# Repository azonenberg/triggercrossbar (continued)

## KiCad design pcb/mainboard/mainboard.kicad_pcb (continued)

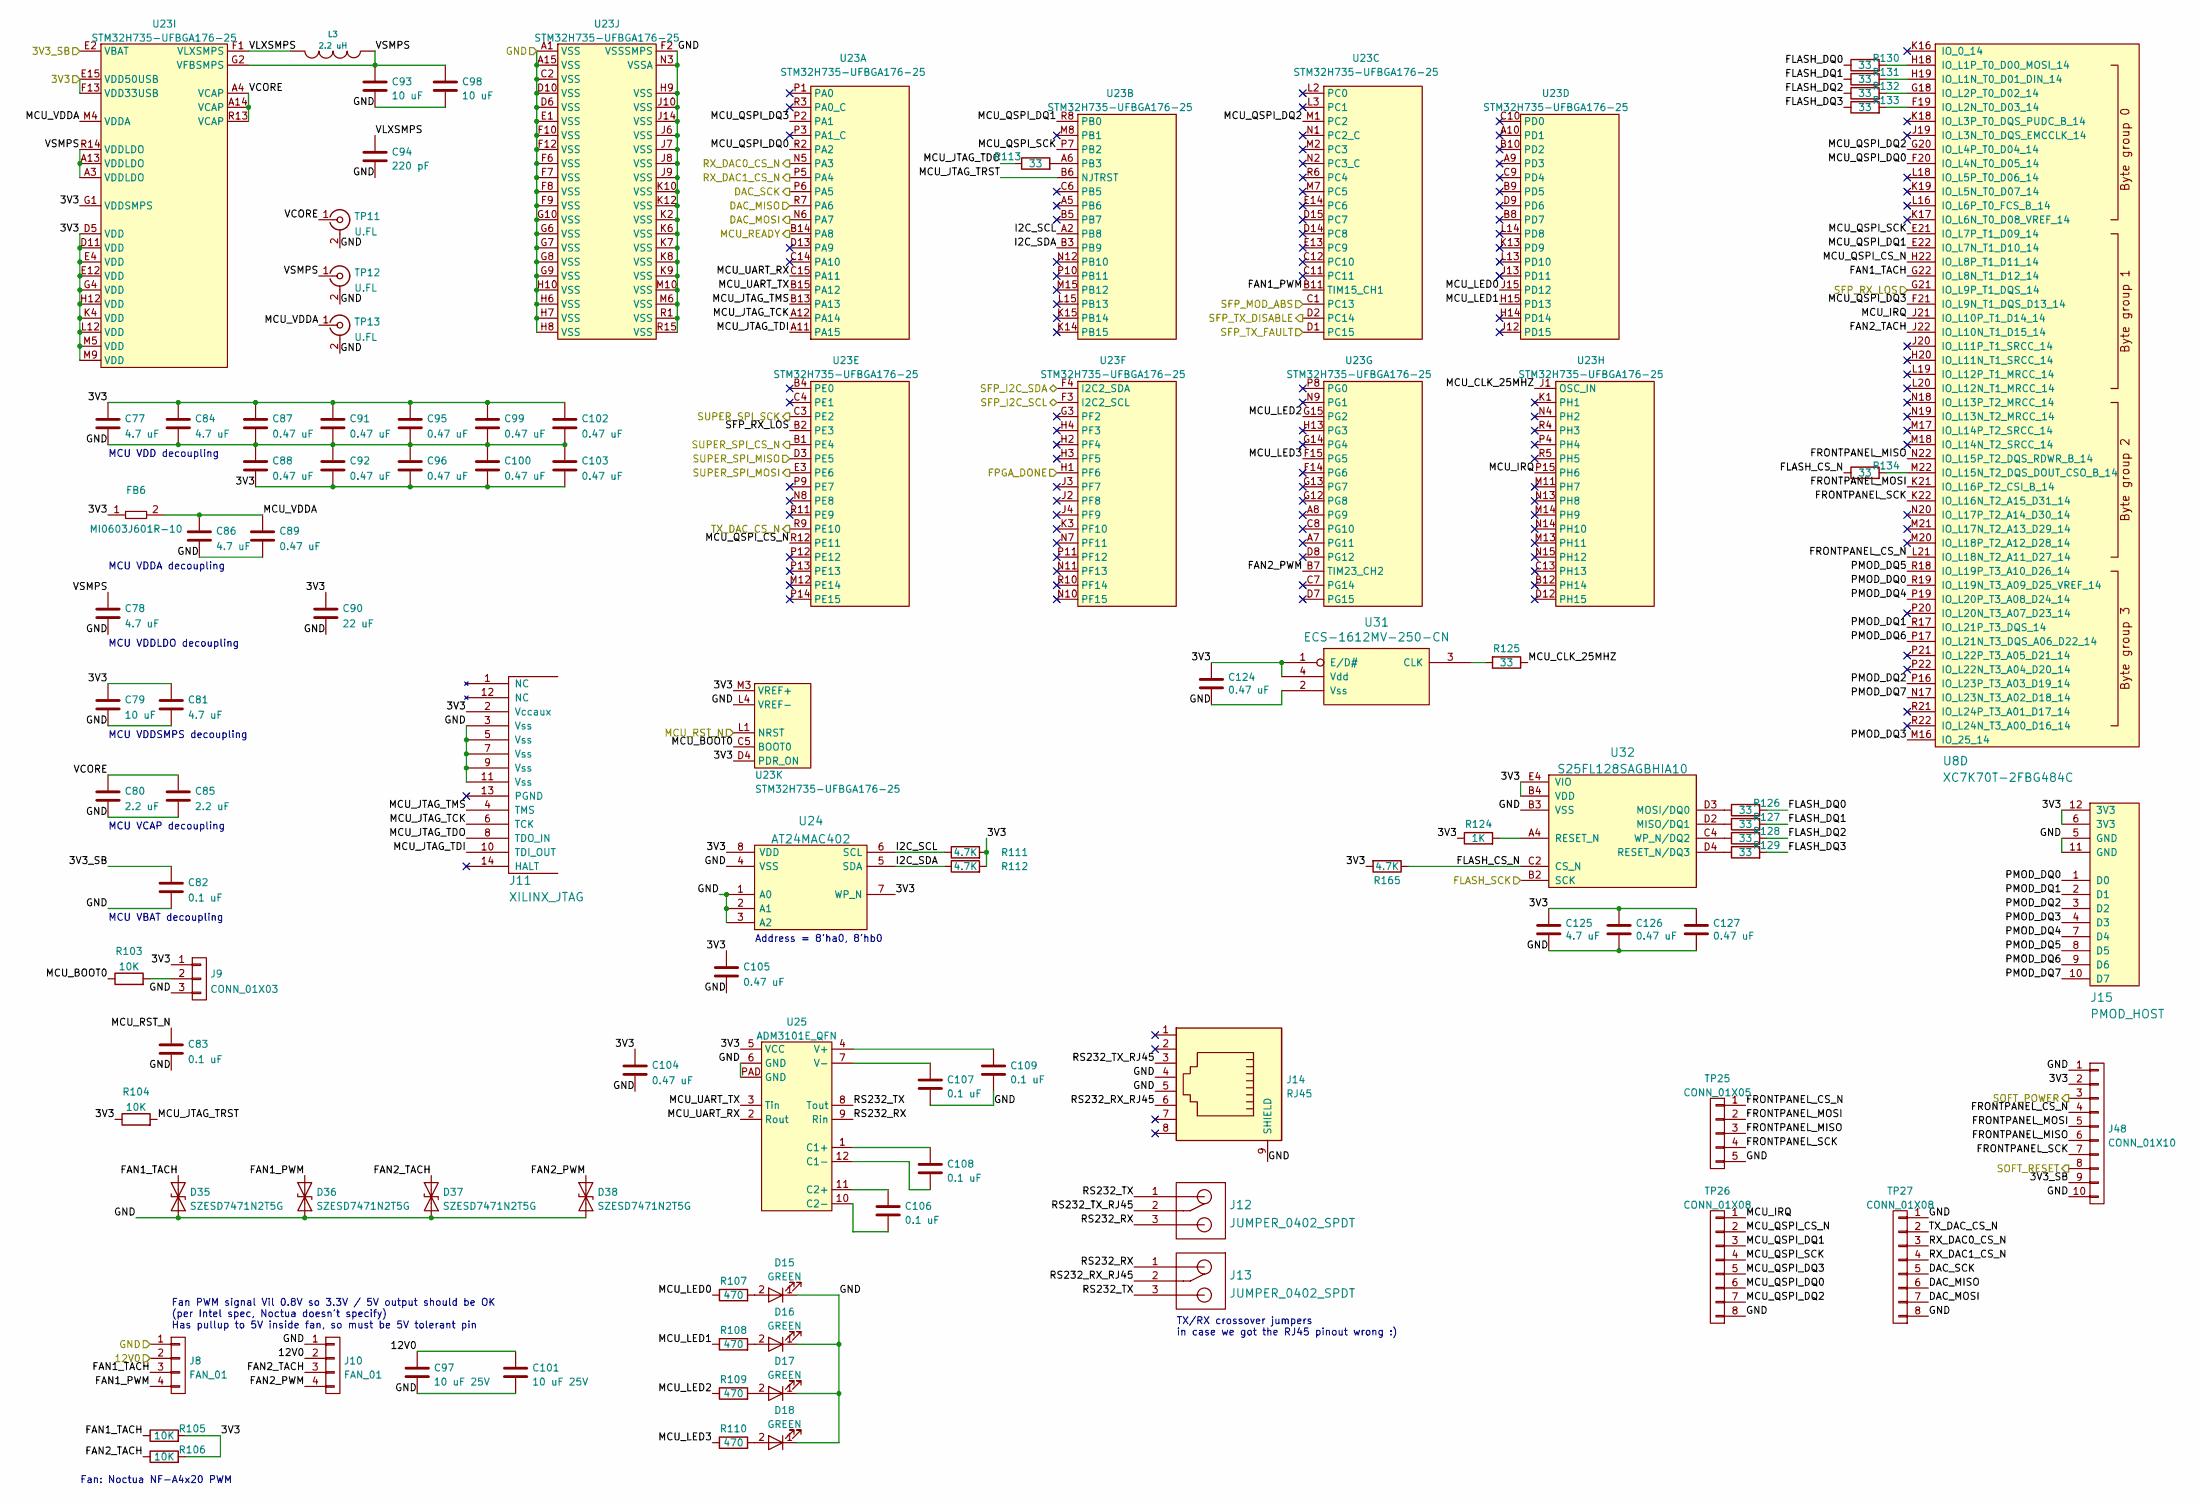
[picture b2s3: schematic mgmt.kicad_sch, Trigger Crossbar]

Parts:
C77, C78, C81, C84, C86, C125: 4.7 uF; EIA_0603_CAP_NOSILK
C79, C93, C98: 10 uF; EIA_0805_CAP_NOSILK
C80, C85: 2.2 uF; EIA_0805_CAP_NOSILK
C82, C83, C106, C107, C108, C109: 0.1 uF; EIA_0402_CAP_NOSILK
C87, C88, C89, C91, C92, C95, C96, C99, C100, C102, C103, C104, C105, C124, C126, C127: 0.47 uF; EIA_0402_CAP_NOSILK
C90: 22 uF; EIA_0805_CAP_NOSILK
C94: 220 pF; EIA_0402_CAP_NOSILK
C97, C101: 10 uF 25V; EIA_1210_CAP_NOSILK
D15, D16, D17, D18: GREEN; EIA_0603_LED
D35, D36, D37, D38: SZESD7471N2T5G; SOD882
FB6: MI0603J601R-10; EIA_0603_INDUCTOR_NOSILK
J8, J10: FAN_01; CONN_MOLEX_KK_0470531000
J9: CONN_01X03; CONN_HEADER_2.54MM_1x3
J11: XILINX_JTAG; XILINX_JTAG_PTH_MOLEX_0878311420
J12, J13: JUMPER_0402_SPDT; EIA_0402_JUMPER
J14: RJ45; CONN_RJ45_BELSTEWART_SS-7188S-A-PG4-1-BA-xx
J15: PMOD_HOST; CONN_HEADER_2.54MM_2x6_RA_PMOD_HOST
J48: CONN_01X10; CONN_MOLEX_PICOBLADE_10POS_0532611071
L3: 2.2 uH; EIA_1210_CAP_NOSILK
R103, R104, R105, R106: 10K; EIA_0402_RES_NOSILK
R107, R108, R109, R110: 470; EIA_0402_RES_NOSILK
R111, R112, R165: 4.7K; EIA_0402_RES_NOSILK
R113, R125, R126, R127, R128, R129, R130, R131, R132, R133, R134: 33; EIA_0402_RES_NOSILK
R124: 1K; EIA_0402_RES_NOSILK
TP11, TP12, TP13: U.FL; CONN_U.FL_TE_1909763-1
TP25: CONN_01X05; CONN_HEADER_2.54MM_1x5
TP26, TP27: CONN_01X08; CONN_HEADER_2.54MM_1x8
U8: XC7K70T-2FBG484C; BGA_484_22x22_FULLARRAY_1MM
U23: STM32H735-UFBGA176-25; BGA_201_10x10_DEPOP_0.65MM_OSHPARK
U24: AT24MAC402; DFN_8_0.5MM_2x3MM_TALL
U25: ADM3101E_QFN; QFN_12_0.5MM_3x3MM
U31: ECS-1612MV-250-CN; OSCILLATOR_1.6x1.2
U32: S25FL128SAGBHIA10; BGA_24_6x8_DEPOP1_1MM

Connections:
/3V3: C77.1, C79.1, C81.1, C84.1, C87.1, C88.2, C90.1, C91.1, C92.2, C95.1, C96.2, C99.1, C100.2, C102.1, C103.2, C104.1, C105.1, C124.1, C125.1, C126.1, C127.1, FB6.1, J9.1, J11.2 (Vccaux), J15.6 (3V3), J15.12 (3V3), J48.2, R104.1, R105.2, R106.2, R111.2, R112.2, R124.1, R165.2, U23.D4 (PDR_ON), U23.D5 (VDD), U23.D11 (VDD), U23.E4 (VDD), U23.E12 (VDD), U23.E15 (VDD50USB), U23.F13 (VDD33USB), U23.G1 (VDDSMPS), U23.G4 (VDD), U23.H12 (VDD), U23.K4 (VDD), U23.L12 (VDD), U23.M3 (VREF+), U23.M5 (VDD), U23.M9 (VDD), U24.7 (WP_N), U24.8 (VDD), U25.5 (VCC), U31.1 (E/D#), U31.4 (Vdd), U32.B4 (VDD), U32.E4 (VIO); also elsewhere on the board
/3V3_SB: C82.1, J48.9, U23.E2 (VBAT); also elsewhere on the board
/12V0: C97.1, C101.1, J8.2, J10.2; also elsewhere on the board
/DAC_MISO: TP27.6, U23.R7 (PA6); also elsewhere on the board
/DAC_MOSI: TP27.7, U23.N6 (PA7); also elsewhere on the board
/DAC_SCK: TP27.5, U23.P6 (PA5); also elsewhere on the board
/FLASH_SCK: U32.B2 (SCK); also elsewhere on the board
/FPGA_DONE: U23.H1 (PF6); also elsewhere on the board
/GND: C77.2, C78.2, C79.2, C80.2, C81.2, C82.2, C83.2, C84.2, C85.2, C86.2, C87.2, C88.1, C89.2, C90.2, C91.2, C92.1, C93.2, C94.2, C95.2, C96.1, C97.2, C98.2, C99.2, C100.1, C101.2, C102.2, C103.1, C104.2, C105.2, C107.2, C109.2, C124.2, C125.2, C126.2, C127.2, D15.1 (K), D16.1 (K), D17.1 (K), D18.1 (K), D35.1 (A1), D36.1 (A1), D37.1 (A1), D38.1 (A1), J8.1, J9.3, J10.1, J11.3 (Vss), J11.5 (Vss), J11.7 (Vss), J11.9 (Vss), J11.11 (Vss), J14.4, J14.5, J14.9 (SHIELD), J15.5 (GND), J15.11 (GND), J48.1, J48.10, TP11.2 (Ext), TP12.2 (Ext), TP13.2 (Ext), TP25.5, TP26.8, TP27.1, TP27.8, U23.A1 (VSS), U23.A15 (VSS), U23.C2 (VSS), U23.D6 (VSS), U23.D10 (VSS), U23.E1 (VSS), U23.F2 (VSSSMPS), U23.F6 (VSS), U23.F7 (VSS), U23.F8 (VSS), U23.F9 (VSS), U23.F10 (VSS), U23.F12 (VSS), U23.G6 (VSS), U23.G7 (VSS), U23.G8 (VSS), U23.G9 (VSS), U23.G10 (VSS), U23.H6 (VSS), U23.H7 (VSS), U23.H8 (VSS), U23.H9 (VSS), U23.H10 (VSS), U23.J6 (VSS), U23.J7 (VSS), U23.J8 (VSS), U23.J9 (VSS), U23.J10 (VSS), U23.J14 (VSS), U23.K2 (VSS), U23.K6 (VSS), U23.K7 (VSS), U23.K8 (VSS), U23.K9 (VSS), U23.K10 (VSS), U23.K12 (VSS), U23.L4 (VREF-), U23.M6 (VSS), U23.M10 (VSS), U23.N3 (VSSA), U23.R1 (VSS), U23.R15 (VSS), U24.1 (A0), U24.2 (A1), U24.3 (A2), U24.4 (VSS), U25.6 (GND), U25.PAD (GND), U31.2 (Vss), U32.B3 (VSS); also elsewhere on the board
/MCU_READY: U23.B14 (PA8); also elsewhere on the board
/MCU_RST_N: C83.1, U23.L1 (NRST); also elsewhere on the board
/Management/FAN1_PWM: D36.2 (A2), J8.4, U23.B11 (TIM15_CH1)
/Management/FAN1_TACH: D35.2 (A2), J8.3, R105.1, U8.G22 (IO_L8N_T1_D12_14)
/Management/FAN2_PWM: D38.2 (A2), J10.4, U23.B7 (TIM23_CH2)
/Management/FAN2_TACH: D37.2 (A2), J10.3, R106.1, U8.J22 (IO_L10N_T1_D15_14)
/Management/FLASH_CS_N: R134.1, R165.1, U32.C2 (CS_N)
/Management/FLASH_DQ0: R126.2, R130.1
/Management/FLASH_DQ1: R127.2, R131.1
/Management/FLASH_DQ2: R128.2, R132.1
/Management/FLASH_DQ3: R129.2, R133.1
/Management/FRONTPANEL_CS_N: J48.4, TP25.1, U8.L21 (IO_L18N_T2_A11_D27_14)
/Management/FRONTPANEL_MISO: J48.6, TP25.3, U8.N22 (IO_L15P_T2_DQS_RDWR_B_14)
/Management/FRONTPANEL_MOSI: J48.5, TP25.2, U8.K21 (IO_L16P_T2_CSI_B_14)
/Management/FRONTPANEL_SCK: J48.7, TP25.4, U8.K22 (IO_L16N_T2_A15_D31_14)
/Management/I2C_SCL: R111.1, U23.A2 (PB8), U24.6 (SCL)
/Management/I2C_SDA: R112.1, U23.B3 (PB9), U24.5 (SDA)
/Management/MCU_BOOT0: R103.1, U23.C5 (BOOT0)
/Management/MCU_CLK_25MHZ: R125.1, U23.J1 (OSC_IN)
/Management/MCU_IRQ: TP26.1, U8.J21 (IO_L10P_T1_D14_14), U23.P15 (PH6)
/Management/MCU_JTAG_TCK: J11.6 (TCK), U23.A12 (PA14)
/Management/MCU_JTAG_TDI: J11.10 (TDI_OUT), U23.A11 (PA15)
/Management/MCU_JTAG_TDO: J11.8 (TDO_IN), R113.1
/Management/MCU_JTAG_TMS: J11.4 (TMS), U23.B13 (PA13)
/Management/MCU_JTAG_TRST: R104.2, U23.B6 (NJTRST)
/Management/MCU_LED0: R107.1, U23.J15 (PD12)
/Management/MCU_LED1: R108.1, U23.H15 (PD13)
/Management/MCU_LED2: R109.1, U23.G15 (PG2)
/Management/MCU_LED3: R110.1, U23.F15 (PG5)
/Management/MCU_QSPI_CS_N: TP26.2, U8.H22 (IO_L8P_T1_D11_14), U23.R12 (PE11)
/Management/MCU_QSPI_DQ0: TP26.6, U8.F20 (IO_L4N_T0_D05_14), U23.R2 (PA2)
/Management/MCU_QSPI_DQ1: TP26.3, U8.E22 (IO_L7N_T1_D10_14), U23.R8 (PB0)
/Management/MCU_QSPI_DQ2: TP26.7, U8.G20 (IO_L4P_T0_D04_14), U23.M1 (PC2)
/Management/MCU_QSPI_DQ3: TP26.5, U8.F21 (IO_L9N_T1_DQS_D13_14), U23.P2 (PA1)
/Management/MCU_QSPI_SCK: TP26.4, U8.E21 (IO_L7P_T1_D09_14), U23.P7 (PB2)
/Management/MCU_UART_RX: U23.C15 (PA11), U25.2 (Rout)
/Management/MCU_UART_TX: U23.B15 (PA12), U25.3 (Tin)
/Management/MCU_VDDA: C86.1, C89.1, FB6.2, TP13.1 (In), U23.M4 (VDDA)
/Management/PMOD_DQ0: J15.1 (D0), U8.R19 (IO_L19N_T3_A09_D25_VREF_14)
/Management/PMOD_DQ1: J15.2 (D1), U8.R17 (IO_L21P_T3_DQS_14)
/Management/PMOD_DQ2: J15.3 (D2), U8.P16 (IO_L23P_T3_A03_D19_14)
/Management/PMOD_DQ3: J15.4 (D3), U8.M16 (IO_25_14)
/Management/PMOD_DQ4: J15.7 (D4), U8.P19 (IO_L20P_T3_A08_D24_14)
/Management/PMOD_DQ5: J15.8 (D5), U8.R18 (IO_L19P_T3_A10_D26_14)
/Management/PMOD_DQ6: J15.9 (D6), U8.P17 (IO_L21N_T3_DQS_A06_D22_14)
/Management/PMOD_DQ7: J15.10 (D7), U8.N17 (IO_L23N_T3_A02_D18_14)
/Management/RS232_RX: J12.3, J13.1, U25.9 (Rin)
/Management/RS232_RX_RJ45: J13.2, J14.6
/Management/RS232_TX: J12.1, J13.3, U25.8 (Tout)
/Management/RS232_TX_RJ45: J12.2, J14.3
/Management/RX_DAC0_CS_N: TP27.3, U23.N5 (PA3); also elsewhere on the board
/Management/RX_DAC1_CS_N: TP27.4, U23.P5 (PA4); also elsewhere on the board
/Management/SFP_MOD_ABS: U23.C1 (PC13); also elsewhere on the board
/Management/SFP_RX_LOS: U8.G21 (IO_L9P_T1_DQS_14), U23.B2 (PE3); also elsewhere on the board
/Management/SFP_TX_DISABLE: U23.D2 (PC14); also elsewhere on the board
/Management/SFP_TX_FAULT: U23.D1 (PC15); also elsewhere on the board
/Management/VCORE: C80.1, C85.1, TP11.1 (In), U23.A4 (VCAP), U23.A14 (VCAP), U23.R13 (VCAP)
/Management/VLXSMPS: C94.1, L3.2, U23.F1 (VLXSMPS)
/Management/VSMPS: C78.1, C93.1, C98.1, L3.1, TP12.1 (In), U23.A3 (VDDLDO), U23.A13 (VDDLDO), U23.G2 (VFBSMPS), U23.R14 (VDDLDO)
/SOFT_POWER: J48.3; also elsewhere on the board
/SOFT_RESET: J48.8; also elsewhere on the board
/SUPER_SPI_CS_N: U23.B1 (PE4); also elsewhere on the board
/SUPER_SPI_MISO: U23.D3 (PE5); also elsewhere on the board
/SUPER_SPI_MOSI: U23.E3 (PE6); also elsewhere on the board
/SUPER_SPI_SCK: U23.C3 (PE2); also elsewhere on the board
/TX_DAC_CS_N: TP27.2, U23.R9 (PE10); also elsewhere on the board
/Transceivers/SFP_I2C_SCL: U23.F3 (I2C2_SCL); also elsewhere on the board
/Transceivers/SFP_I2C_SDA: U23.F4 (I2C2_SDA); also elsewhere on the board
unnamed: C106.1, U25.11 (C2+)
unnamed: C106.2, U25.10 (C2-)
unnamed: C107.1, U25.7 (V-)
unnamed: C108.1, U25.1 (C1+)
unnamed: C108.2, U25.12 (C1-)
unnamed: C109.1, U25.4 (V+)
unnamed: D15.2 (A), R107.2
unnamed: D16.2 (A), R108.2
unnamed: D17.2 (A), R109.2
unnamed: D18.2 (A), R110.2
unnamed: J9.2, R103.2
unnamed: R113.2, U23.A6 (PB3)
unnamed: R124.2, U32.A4 (RESET_N)
unnamed: R125.2, U31.3 (CLK)
unnamed: R126.1, U32.D3 (MOSI/DQ0)
unnamed: R127.1, U32.D2 (MISO/DQ1)
unnamed: R128.1, U32.C4 (WP_N/DQ2)
unnamed: R129.1, U32.D4 (RESET_N/DQ3)
unnamed: R130.2, U8.H18 (IO_L1P_T0_D00_MOSI_14)
unnamed: R131.2, U8.H19 (IO_L1N_T0_D01_DIN_14)
unnamed: R132.2, U8.G18 (IO_L2P_T0_D02_14)
unnamed: R133.2, U8.F19 (IO_L2N_T0_D03_14)
unnamed: R134.2, U8.M22 (IO_L15N_T2_DQS_DOUT_CSO_B_14)

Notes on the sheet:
MCU VCAP decoupling
MCU VDDLDO decoupling
MCU VDDSMPS decoupling
MCU VDD decoupling
Fan: Noctua NF-A4x20 PWM
MCU VDDA decoupling
Fan PWM signal Vil 0.8V so 3.3V / 5V output should be OK (per Intel spec, Noctua doesn't specify) Has pullup to 5V inside fan, so must be 5V tolerant pin
Address = 8'ha0, 8'hb0
MCU VBAT decoupling
TX/RX crossover jumpers in case we got the RJ45 pinout wrong :)

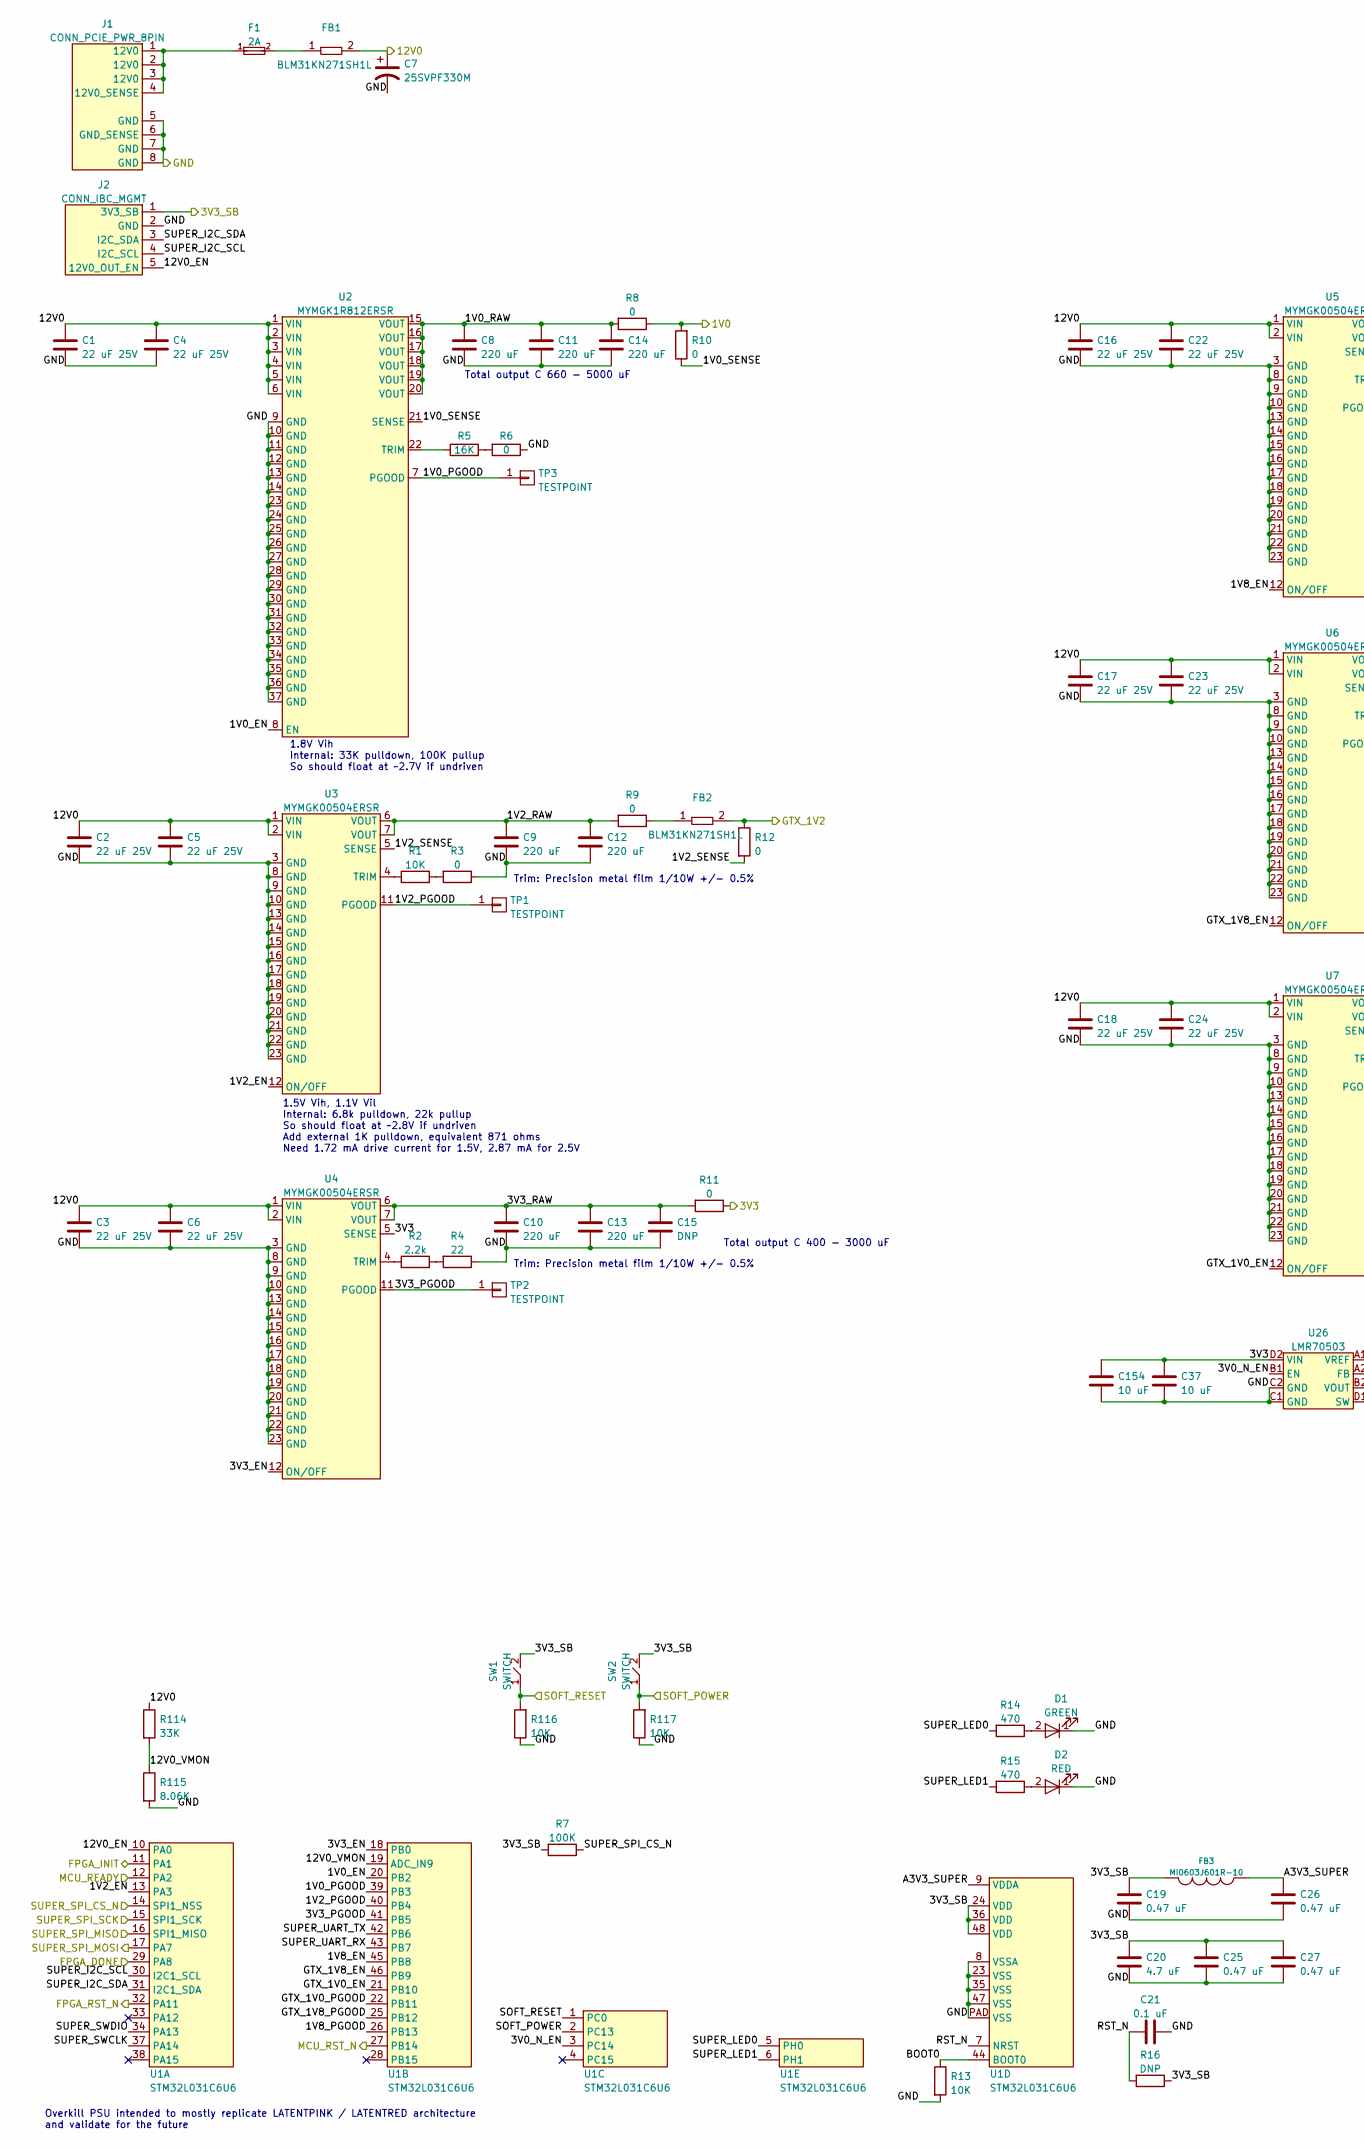
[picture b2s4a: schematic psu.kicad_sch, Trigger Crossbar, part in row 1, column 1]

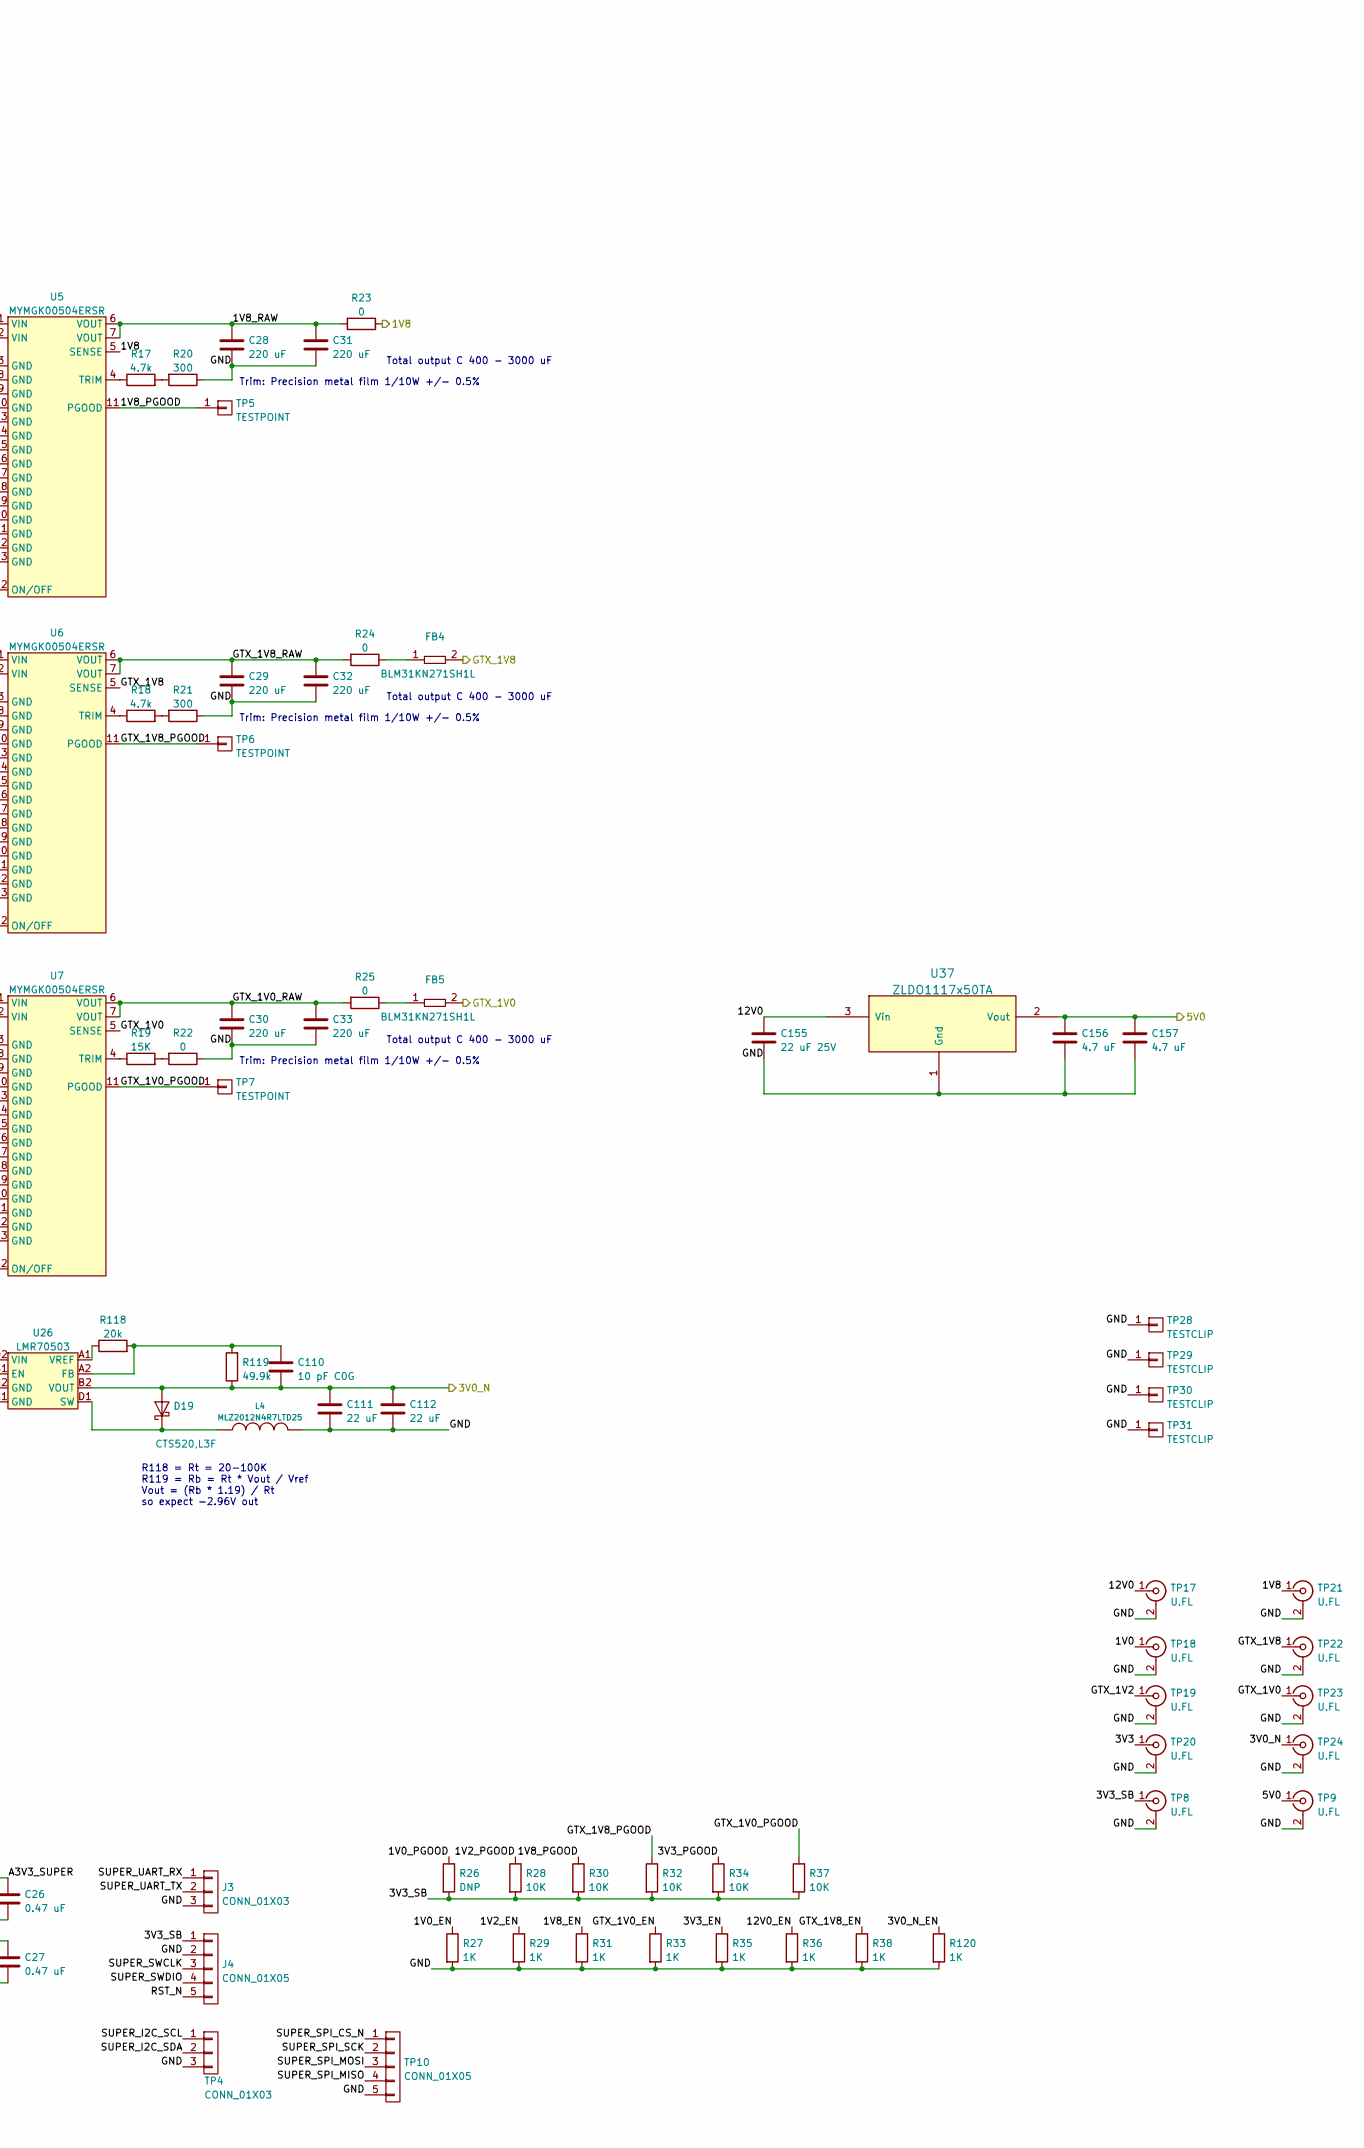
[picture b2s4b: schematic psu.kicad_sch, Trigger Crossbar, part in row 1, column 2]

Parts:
C1, C2, C3, C4, C5, C6, C16, C17, C18, C22, C23, C24, C155: 22 uF 25V; EIA_1812_CAP_NOSILK
C7: 25SVPF330M; CAP_AL_10MM_SMT
C8, C9, C10, C11, C12, C13, C14, C28, C29, C30, C31, C32, C33: 220 uF; EIA_1210_CAP_NOSILK
C15: DNP; EIA_1210_CAP_NOSILK
C19, C25, C26, C27: 0.47 uF; EIA_0402_CAP_NOSILK
C20, C156, C157: 4.7 uF; EIA_0603_CAP_NOSILK
C21: 0.1 uF; EIA_0402_CAP_NOSILK
C37, C154: 10 uF; EIA_0805_CAP_NOSILK
C110: 10 pF C0G; EIA_0402_CAP_NOSILK
C111, C112: 22 uF; EIA_0805_CAP_NOSILK
D1: GREEN; EIA_0603_LED
D2: RED; EIA_0603_LED
D19: CTS520,L3F; SOD882
F1: 2A; EIA_0603_CAP_NOSILK
FB1, FB2, FB4, FB5: BLM31KN271SH1L; EIA_1206_CAP_NOSILK
FB3: MI0603J601R-10; EIA_0603_INDUCTOR_NOSILK
J1: CONN_PCIE_PWR_8PIN; CONN_MOLEX_MINIFITJR_8POS_0039291087
J2: CONN_IBC_MGMT; CONN_MOLEX_PICOBLADE_5POS_0532610571
J3: CONN_01X03; CONN_HEADER_2.54MM_1x3
J4: CONN_01X05; CONN_HEADER_2.54MM_1x5
L4: MLZ2012N4R7LTD25; EIA_0805_INDUCTOR_NOSILK
R1, R13, R28, R30, R32, R34, R37, R116, R117: 10K; EIA_0402_RES_NOSILK
R2: 2.2k; EIA_0402_RES_NOSILK
R3, R6, R8, R9, R10, R11, R12, R22, R23, R24, R25: 0; EIA_0402_RES_NOSILK
R4: 22; EIA_0402_RES_NOSILK
R5: 16K; EIA_0402_RES_NOSILK
R7: 100K; EIA_0402_RES_NOSILK
R14, R15: 470; EIA_0402_RES_NOSILK
R16, R26: DNP; EIA_0402_RES_NOSILK
R17, R18: 4.7k; EIA_0402_RES_NOSILK
R19: 15K; EIA_0402_RES_NOSILK
R20, R21: 300; EIA_0402_RES_NOSILK
R27, R29, R31, R33, R35, R36, R38, R120: 1K; EIA_0402_RES_NOSILK
R114: 33K; EIA_0402_RES_NOSILK
R115: 8.06K; EIA_0402_RES_NOSILK
R118: 20k; EIA_0402_RES_NOSILK
R119: 49.9k; EIA_0402_RES_NOSILK
SW1, SW2: SWITCH; SWITCH_RAFI_MICON_5
TP1, TP2, TP3, TP5, TP6, TP7: TESTPOINT; TESTPOINT_SMT_0.5MM
TP4: CONN_01X03; CONN_HEADER_2.54MM_1x3
TP8, TP9, TP17, TP18, TP19, TP20, TP21, TP22, TP23, TP24: U.FL; CONN_U.FL_TE_1909763-1
TP10: CONN_01X05; CONN_HEADER_2.54MM_1x5
TP28, TP29, TP30, TP31: TESTCLIP; TESTPOINT_SMT_KEYSTONE_5016
U1: STM32L031C6U6; QFN_48_0.5MM_7x7MM
U2: MYMGK1R812ERSR; MODULE_MURATA_MYMGK1R812
U3, U4, U5, U6, U7: MYMGK00504ERSR; MODULE_MURATA_MYMGK00504ERSR
U26: LMR70503; BGA_8_1.65x0.865_0.4MM_TI_YFX
U37: ZLDO1117x50TA; SOT223-4

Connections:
/1V2: FB2.2, R12.1, TP19.1 (In); also elsewhere on the board
/3V0_N: C110.2, C111.1, C112.1, D19.2 (A), R119.1, TP24.1 (In), U26.B2 (VOUT); also elsewhere on the board
/3V3: C37.1, C154.1, R11.1, TP20.1 (In), U4.5 (SENSE), U26.D2 (VIN); also elsewhere on the board
/3V3_SB: C19.1, C20.1, C25.1, C27.1, FB3.2, J2.1 (3V3_SB), J4.1, R7.2, R16.1, R26.2, R28.2, R30.2, R32.2, R34.2, R37.2, SW1.2, SW2.2, TP8.1 (In), U1.24 (VDD), U1.36 (VDD), U1.48 (VDD); also elsewhere on the board
/5V0: C156.1, C157.1, TP9.1 (In), U37.2 (Vout); also elsewhere on the board
/12V0: C1.1, C2.1, C3.1, C4.1, C5.1, C6.1, C7.1, C16.1, C17.1, C18.1, C22.1, C23.1, C24.1, C155.1, FB1.2, R114.1, TP17.1 (In), U2.1 (VIN), U2.2 (VIN), U2.3 (VIN), U2.4 (VIN), U2.5 (VIN), U2.6 (VIN), U3.1 (VIN), U3.2 (VIN), U4.1 (VIN), U4.2 (VIN), U5.1 (VIN), U5.2 (VIN), U6.1 (VIN), U6.2 (VIN), U7.1 (VIN), U7.2 (VIN), U37.3 (Vin); also elsewhere on the board
/FPGA Support/1V0: R8.1, R10.2, TP18.1 (In); also elsewhere on the board
/FPGA Support/FPGA_INIT: U1.11 (PA1); also elsewhere on the board
/FPGA Support/FPGA_RST_N: U1.32 (PA11); also elsewhere on the board
/FPGA Support/GTX_1V0: FB5.2, TP23.1 (In), U7.5 (SENSE); also elsewhere on the board
/FPGA Support/GTX_1V8: FB4.2, TP22.1 (In), U6.5 (SENSE); also elsewhere on the board
/FPGA_DONE: U1.29 (PA8); also elsewhere on the board
/GND: C1.2, C2.2, C3.2, C4.2, C5.2, C6.2, C7.2, C8.2, C9.2, C10.2, C11.2, C12.2, C13.2, C14.2, C15.2, C16.2, C17.2, C18.2, C19.2, C20.2, C21.2, C22.2, C23.2, C24.2, C25.2, C26.2, C27.2, C28.2, C29.2, C30.2, C31.2, C32.2, C33.2, C37.2, C111.2, C112.2, C154.2, C155.2, C156.2, C157.2, D1.1 (K), D2.1 (K), J1.5 (GND), J1.6 (GND_SENSE), J1.7 (GND), J1.8 (GND), J2.2 (GND), J3.3, J4.2, L4.2, R3.1, R4.1, R6.1, R13.2, R20.1, R21.1, R22.1, R27.2, R29.2, R31.2, R33.2, R35.2, R36.2, R38.2, R115.2, R116.1, R117.1, R120.2, TP4.3, TP8.2 (Ext), TP9.2 (Ext), TP10.5, TP17.2 (Ext), TP18.2 (Ext), TP19.2 (Ext), TP20.2 (Ext), TP21.2 (Ext), TP22.2 (Ext), TP23.2 (Ext), TP24.2 (Ext), TP28.1, TP29.1, TP30.1, TP31.1, U1.8 (VSSA), U1.23 (VSS), U1.35 (VSS), U1.47 (VSS), U1.PAD (VSS), U2.9 (GND), U2.10 (GND), U2.11 (GND), U2.12 (GND), U2.13 (GND), U2.14 (GND), U2.23 (GND), U2.24 (GND), U2.25 (GND), U2.26 (GND), U2.27 (GND), U2.28 (GND), U2.29 (GND), U2.30 (GND), U2.31 (GND), U2.32 (GND), U2.33 (GND), U2.34 (GND), U2.35 (GND), U2.36 (GND), U2.37 (GND), U3.3 (GND), U3.8 (GND), U3.9 (GND), U3.10 (GND), U3.13 (GND), U3.14 (GND), U3.15 (GND), U3.16 (GND), U3.17 (GND), U3.18 (GND), U3.19 (GND), U3.20 (GND), U3.21 (GND), U3.22 (GND), U3.23 (GND), U4.3 (GND), U4.8 (GND), U4.9 (GND), U4.10 (GND), U4.13 (GND), U4.14 (GND), U4.15 (GND), U4.16 (GND), U4.17 (GND), U4.18 (GND), U4.19 (GND), U4.20 (GND), U4.21 (GND), U4.22 (GND), U4.23 (GND), U5.3 (GND), U5.8 (GND), U5.9 (GND), U5.10 (GND), U5.13 (GND), U5.14 (GND), U5.15 (GND), U5.16 (GND), U5.17 (GND), U5.18 (GND), U5.19 (GND), U5.20 (GND), U5.21 (GND), U5.22 (GND), U5.23 (GND), U6.3 (GND), U6.8 (GND), U6.9 (GND), U6.10 (GND), U6.13 (GND), U6.14 (GND), U6.15 (GND), U6.16 (GND), U6.17 (GND), U6.18 (GND), U6.19 (GND), U6.20 (GND), U6.21 (GND), U6.22 (GND), U6.23 (GND), U7.3 (GND), U7.8 (GND), U7.9 (GND), U7.10 (GND), U7.13 (GND), U7.14 (GND), U7.15 (GND), U7.16 (GND), U7.17 (GND), U7.18 (GND), U7.19 (GND), U7.20 (GND), U7.21 (GND), U7.22 (GND), U7.23 (GND), U26.C1 (GND), U26.C2 (GND), U37.1 (Gnd); also elsewhere on the board
/MCU_READY: U1.12 (PA2); also elsewhere on the board
/MCU_RST_N: U1.27 (PB14); also elsewhere on the board
/Power Supply/1V0_EN: R27.1, U1.20 (PB2), U2.8 (EN)
/Power Supply/1V0_PGOOD: R26.1, TP3.1, U1.39 (PB3), U2.7 (PGOOD)
/Power Supply/1V0_RAW: C8.1, C11.1, C14.1, R8.2, U2.15 (VOUT), U2.16 (VOUT), U2.17 (VOUT), U2.18 (VOUT), U2.19 (VOUT), U2.20 (VOUT)
/Power Supply/1V0_SENSE: R10.1, U2.21 (SENSE)
/Power Supply/1V2_EN: R29.1, U1.13 (PA3), U3.12 (ON/OFF)
/Power Supply/1V2_PGOOD: R28.1, TP1.1, U1.40 (PB4), U3.11 (PGOOD)
/Power Supply/1V2_RAW: C9.1, C12.1, R9.2, U3.6 (VOUT), U3.7 (VOUT)
/Power Supply/1V2_SENSE: R12.2, U3.5 (SENSE)
/Power Supply/1V8_EN: R31.1, U1.45 (PB8), U5.12 (ON/OFF)
/Power Supply/1V8_PGOOD: R30.1, TP5.1, U1.26 (PB13), U5.11 (PGOOD)
/Power Supply/1V8_RAW: C28.1, C31.1, R23.2, U5.6 (VOUT), U5.7 (VOUT)
/Power Supply/3V0_N_EN: R120.1, U1.3 (PC14), U26.B1 (EN)
/Power Supply/3V3_EN: R35.1, U1.18 (PB0), U4.12 (ON/OFF)
/Power Supply/3V3_PGOOD: R34.1, TP2.1, U1.41 (PB5), U4.11 (PGOOD)
/Power Supply/3V3_RAW: C10.1, C13.1, C15.1, R11.2, U4.6 (VOUT), U4.7 (VOUT)
/Power Supply/12V0_EN: J2.5 (12V0_OUT_EN), R36.1, U1.10 (PA0)
/Power Supply/12V0_VMON: R114.2, R115.1, U1.19 (ADC_IN9)
/Power Supply/A3V3_SUPER: C26.1, FB3.1, U1.9 (VDDA)
/Power Supply/BOOT0: R13.1, U1.44 (BOOT0)
/Power Supply/GTX_1V0_EN: R33.1, U1.21 (PB10), U7.12 (ON/OFF)
/Power Supply/GTX_1V0_PGOOD: R37.1, TP7.1, U1.22 (PB11), U7.11 (PGOOD)
/Power Supply/GTX_1V0_RAW: C30.1, C33.1, R25.2, U7.6 (VOUT), U7.7 (VOUT)
/Power Supply/GTX_1V8_EN: R38.1, U1.46 (PB9), U6.12 (ON/OFF)
/Power Supply/GTX_1V8_PGOOD: R32.1, TP6.1, U1.25 (PB12), U6.11 (PGOOD)
/Power Supply/GTX_1V8_RAW: C29.1, C32.1, R24.2, U6.6 (VOUT), U6.7 (VOUT)
/Power Supply/RST_N: C21.1, J4.5, R16.2, U1.7 (NRST)
/Power Supply/SUPER_I2C_SCL: J2.4 (I2C_SCL), TP4.1, U1.30 (I2C1_SCL)
/Power Supply/SUPER_I2C_SDA: J2.3 (I2C_SDA), TP4.2, U1.31 (I2C1_SDA)
/Power Supply/SUPER_LED0: R14.2, U1.5 (PH0)
/Power Supply/SUPER_LED1: R15.2, U1.6 (PH1)
/Power Supply/SUPER_SWCLK: J4.3, U1.37 (PA14)
/Power Supply/SUPER_SWDIO: J4.4, U1.34 (PA13)
/Power Supply/SUPER_UART_RX: J3.1, U1.43 (PB7)
/Power Supply/SUPER_UART_TX: J3.2, U1.42 (PB6)
/SOFT_POWER: R117.2, SW2.1, U1.2 (PC13); also elsewhere on the board
/SOFT_RESET: R116.2, SW1.1, U1.1 (PC0); also elsewhere on the board
/SUPER_SPI_CS_N: R7.1, TP10.1, U1.14 (SPI1_NSS); also elsewhere on the board
/SUPER_SPI_MISO: TP10.3, U1.17 (PA7); also elsewhere on the board
/SUPER_SPI_MOSI: TP10.4, U1.16 (SPI1_MISO); also elsewhere on the board
/SUPER_SPI_SCK: TP10.2, U1.15 (SPI1_SCK); also elsewhere on the board
unnamed: C110.1, R118.2, R119.2, U26.A2 (FB)
unnamed: D1.2 (A), R14.1
unnamed: D2.2 (A), R15.1
unnamed: D19.1 (K), L4.1, U26.D1 (SW)
unnamed: F1.1, J1.1 (12V0), J1.2 (12V0), J1.3 (12V0), J1.4 (12V0_SENSE)
unnamed: F1.2, FB1.1
unnamed: FB2.1, R9.1
unnamed: FB4.1, R24.1
unnamed: FB5.1, R25.1
unnamed: R1.1, U3.4 (TRIM)
unnamed: R1.2, R3.2
unnamed: R2.1, U4.4 (TRIM)
unnamed: R2.2, R4.2
unnamed: R5.1, U2.22 (TRIM)
unnamed: R5.2, R6.2
unnamed: R17.1, U5.4 (TRIM)
unnamed: R17.2, R20.2
unnamed: R18.1, U6.4 (TRIM)
unnamed: R18.2, R21.2
unnamed: R19.1, U7.4 (TRIM)
unnamed: R19.2, R22.2
unnamed: R118.1, U26.A1 (VREF)

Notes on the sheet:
Trim: Precision metal film 1/10W +/- 0.5%
Total output C 400 - 3000 uF
Overkill PSU intended to mostly replicate LATENTPINK / LATENTRED architecture and validate for the future
R118 = Rt = 20-100K R119 = Rb = Rt * Vout / Vref Vout = (Rb * 1.19) / Rt so expect -2.96V out
1.8V Vih Internal: 33K pulldown, 100K pullup So should float at ~2.7V if undriven
Total output C 660 - 5000 uF
1.5V Vih, 1.1V Vil Internal: 6.8k pulldown, 22k pullup So should float at ~2.8V if undriven Add external 1K pulldown, equivalent 871 ohms Need 1.72 mA drive current for 1.5V, 2.87 mA for 2.5V
